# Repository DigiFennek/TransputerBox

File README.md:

# TransputerBox
This is the DosBox based TransputerBox

The interface is based on a LPC dual-core MPU. The Cortex-M4 is doing USB stuff while the Cortex-M0+ is talking to the IMSC012 Transpuer Link Interface. The MCU is also checking the health status of the power supply and the cooling system.

The host-side is based on a modified version of DOSBox. It emulates the IMSB008 or IMSB004 hardware and connets to the TransputerBox via USB.

Software:
  - DOSBox with USB-Bridge, Windows 10, Visual Studio 2019: [Link](https://github.com/DigiFennek/TransputerBox/tree/master/Visual%20Studio)
  - USB-Interface, based on NXP's LPC54114, MCUXPresso IDE v11: [Link](https://github.com/DigiFennek/TransputerBox/tree/master/MCUXpresso)
  - CPLD for the fancy Link-Leds, Lattice M4A5-64/32-10VC, ispLever Classic: [Link](https://github.com/DigiFennek/TransputerBox/tree/master/ispLEVER%20Classic/linkled)
  
Hardware:
  - Module for 4 TRAM's, Eagle Layout Editor: [Link](https://github.com/DigiFennek/TransputerBox/tree/master/Eagle/TB-4)
  - Backpanel with 7 slots, Eagle Layout Editor: [Link](https://github.com/DigiFennek/TransputerBox/tree/master/Eagle/BB-7)
  - USB Interface with Power Management, Current Sensor and HP-Display, Eagle Layout Editor: [Link](https://github.com/DigiFennek/TransputerBox/tree/master/Eagle/UB-1)
  - SIZE-1 TRAM with 128kB SRAM, Eagle Layout Editor: [Link](https://github.com/DigiFennek/TransputerBox/tree/master/Eagle/TM-2)    
  
Misc
  - Front Panels, www.schaeffer-ag.de "FRONTPLATTEN DESIGNER": [Link](https://github.com/DigiFennek/TransputerBox/tree/master/Schaeffer%20AG)

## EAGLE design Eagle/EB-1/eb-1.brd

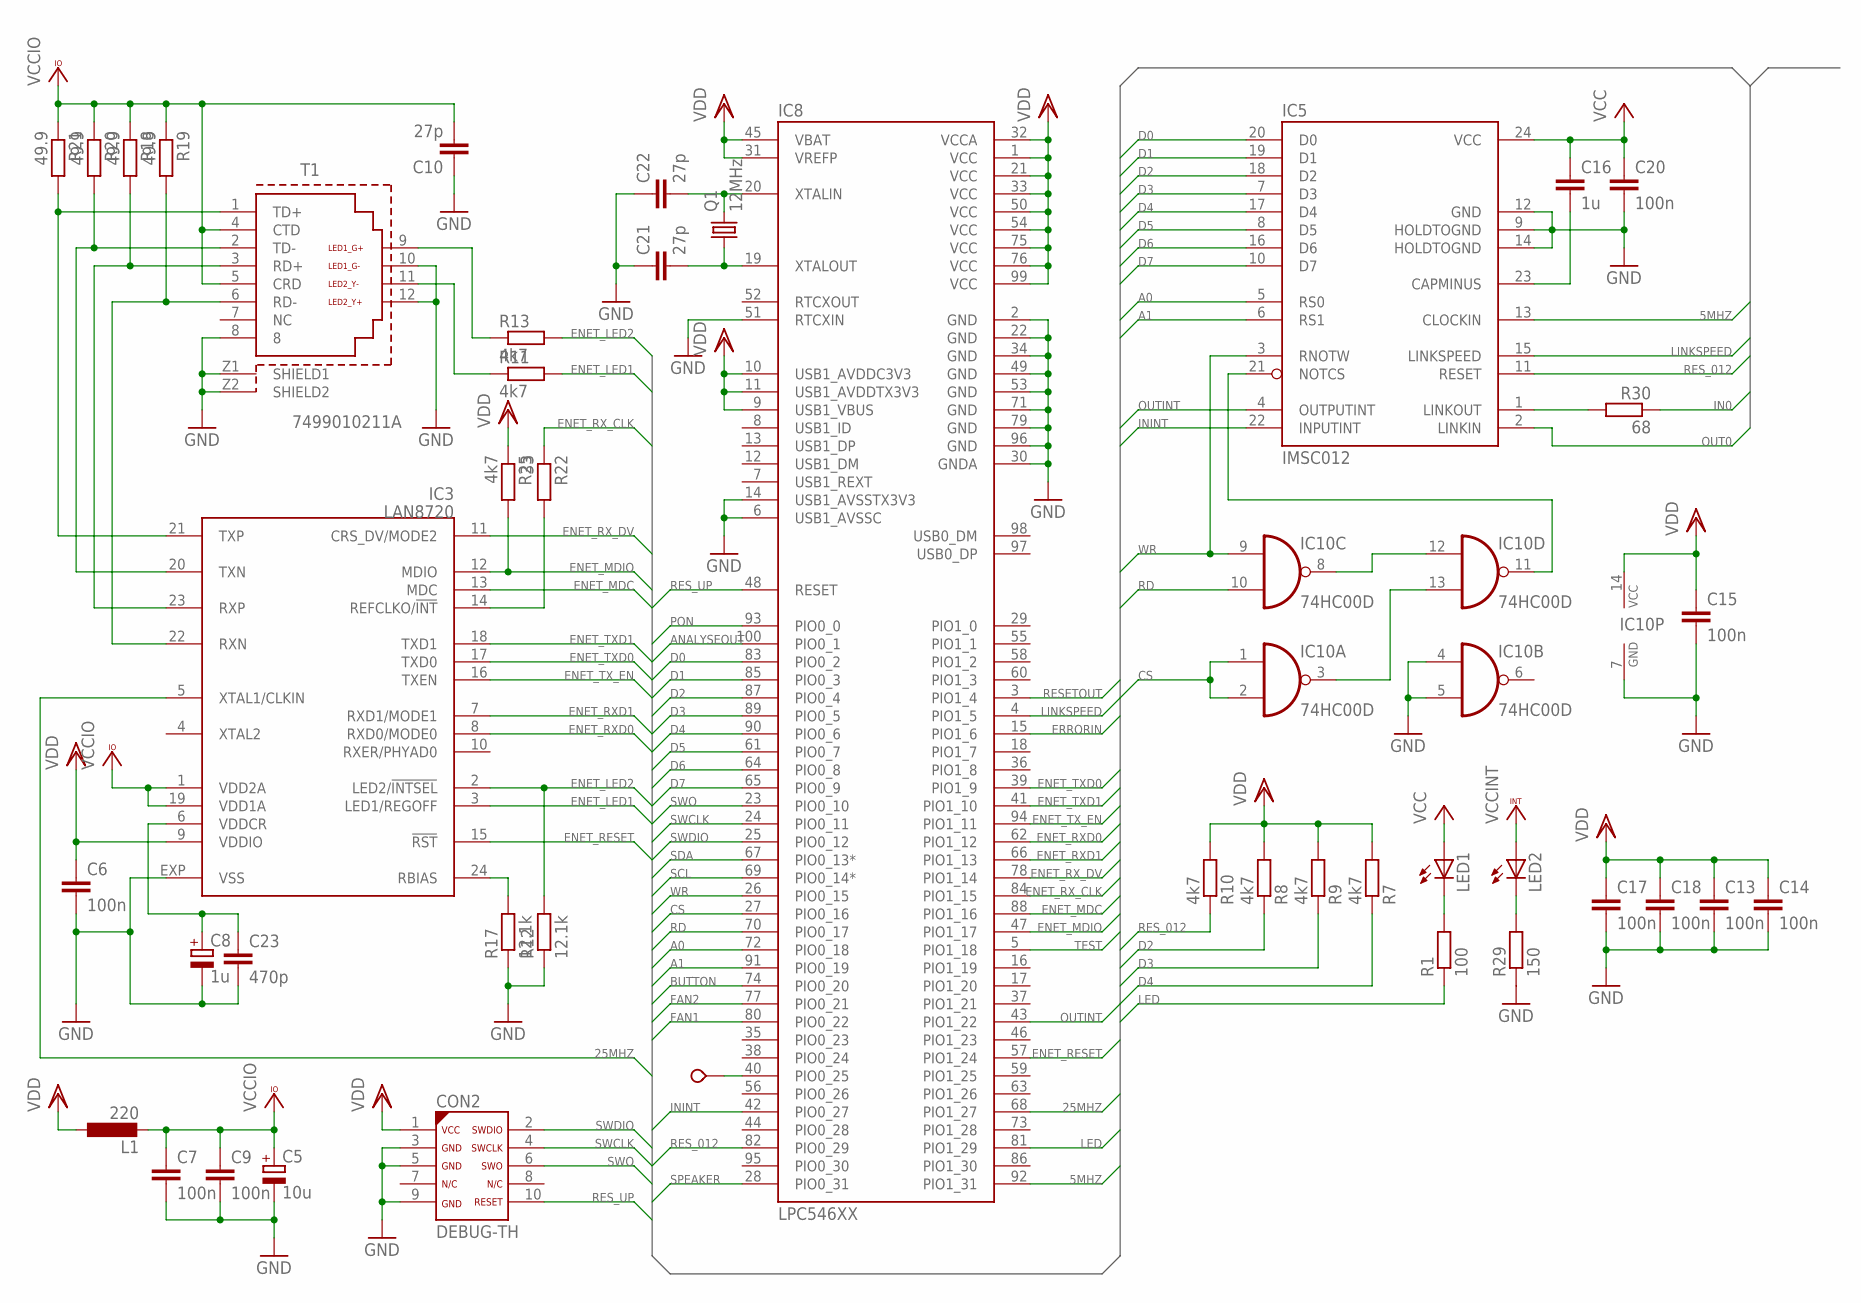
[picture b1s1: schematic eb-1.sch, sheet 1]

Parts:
C5: 10u; CT3216
C6, C7, C9, C13, C14, C15, C17, C18, C20: 100n; C1206; DIGIKEY 478-10855-1-ND
C8: 1u; CT3216
C10, C21, C22: 27p; C1206; DIGIKEY 478-10855-1-ND
C16: 1u; C1206; DIGIKEY 478-1567-1-ND
C23: 470p; C1206; DIGIKEY 478-10855-1-ND
CON2: DEBUG-TH; DIGIKEY 1175-1627-ND
IC3: LAN8720; QFN24
IC5: IMSC012; DIL24-3
IC8: LPC546XX; LQFP100
IC10: 74HC00D; SO14
L1: 220; L3216C
LED1, LED2: LEDSMT1206; 1206; DIGIKEY 160-1404-1-ND
Q1: 12MHz; HC49UP
R1: 100; R1206; DIGIKEY CR1206-FX-1000ELFCT-ND
R7, R8, R9, R10, R11, R13, R25: 4k7; R1206; DIGIKEY CR1206-FX-4701ELFCT-ND
R12, R17: 12.1k; R1206; DIGIKEY CR1206-FX-4701ELFCT-ND
R18, R19, R20, R21: 49.9; R1206; DIGIKEY CR1206-FX-4701ELFCT-ND
R22: 33; R1206; DIGIKEY CR1206-FX-4701ELFCT-ND
R29: 150; R1206; DIGIKEY CR1206-FX-1500ELFCT-ND
R30: 68; R1206; DIGIKEY CR1206-FX-68R0ELFCT-ND
T1: 7499010211A
TP2: TESTPOINT; VERO_TP

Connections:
5MHZ: IC5.13 (CLOCKIN), IC8.92 (PIO1_31)
25MHZ: IC3.5 (XTAL1/CLKIN), IC8.68 (PIO1_27)
A0: IC5.5 (RS0), IC8.72 (PIO0_18)
A1: IC5.6 (RS1), IC8.91 (PIO0_19)
ANALYSEOUT: IC8.100 (PIO0_1); also elsewhere on the board
BUTTON: IC8.74 (PIO0_20); also elsewhere on the board
CS: IC8.27 (PIO0_16), IC10.1 (I0), IC10.2 (I1)
D0: IC5.20 (D0), IC8.83 (PIO0_2)
D1: IC5.19 (D1), IC8.85 (PIO0_3)
D2: IC5.18 (D2), IC8.87 (PIO0_4), R8.1
D3: IC5.7 (D3), IC8.89 (PIO0_5), R9.1
D4: IC5.17 (D4), IC8.90 (PIO0_6), R7.1
D5: IC5.8 (D5), IC8.61 (PIO0_7)
D6: IC5.16 (D6), IC8.64 (PIO0_8)
D7: IC5.10 (D7), IC8.65 (PIO0_9)
ENET_LED1: IC3.3 (LED1/REGOFF), R11.2
ENET_LED2: IC3.2 (LED2/!INTSEL), R12.2, R13.2
ENET_MDC: IC3.13 (MDC), IC8.88 (PIO1_16)
ENET_MDIO: IC3.12 (MDIO), IC8.47 (PIO1_17), R25.2
ENET_RESET: IC3.15 (!RST), IC8.57 (PIO1_24)
ENET_RXD0: IC3.8 (RXD0/MODE0), IC8.62 (PIO1_12)
ENET_RXD1: IC3.7 (RXD1/MODE1), IC8.66 (PIO1_13)
ENET_RX_CLK: IC8.84 (PIO1_15), R22.1
ENET_RX_DV: IC3.11 (CRS_DV/MODE2), IC8.78 (PIO1_14)
ENET_TXD0: IC3.17 (TXD0), IC8.39 (PIO1_9)
ENET_TXD1: IC3.18 (TXD1), IC8.41 (PIO1_10)
ENET_TX_EN: IC3.16 (TXEN), IC8.94 (PIO1_11)
ERRORIN: IC8.15 (PIO1_6); also elsewhere on the board
FAN1: IC8.80 (PIO0_22); also elsewhere on the board
FAN2: IC8.77 (PIO0_21); also elsewhere on the board
GND: C5.-, C6.2, C7.2, C8.-, C9.2, C10.1, C13.2, C14.2, C15.2, C17.2, C18.2, C20.2, C21.1, C22.1, C23.2, CON2.3, CON2.5, CON2.9, IC3.EXP (VSS), IC5.9 (HOLDTOGND), IC5.12 (GND), IC5.14 (HOLDTOGND), IC8.2 (GND), IC8.6 (USB1_AVSSC), IC8.14 (USB1_AVSSTX3V3), IC8.22 (GND), IC8.30 (GNDA), IC8.34 (GND), IC8.49 (GND), IC8.51 (RTCXIN), IC8.53 (GND), IC8.71 (GND), IC8.79 (GND), IC8.96 (GND), IC10.4 (I0), IC10.5 (I1), IC10.7 (GND), R12.1, R17.1, R29.1, T1.8, T1.10 (LED1_G-), T1.12 (LED2_Y+), T1.Z1 (SHIELD1), T1.Z2 (SHIELD2); also elsewhere on the board
IN0: R30.1; also elsewhere on the board
ININT: IC5.22 (INPUTINT), IC8.42 (PIO0_27)
LED: IC8.81 (PIO1_29), R1.1
LINKSPEED: IC5.15 (LINKSPEED), IC8.4 (PIO1_5); also elsewhere on the board
unnamed: IC3.14 (REFCLKO/!INT), R22.2
unnamed: R13.1, T1.9 (LED1_G+)
unnamed: IC3.24 (RBIAS), R17.2
unnamed: R11.1, T1.11 (LED2_Y-)
unnamed: IC8.40 (PIO0_25), TP2.P$1
unnamed: C8.+, C23.1, IC3.6 (VDDCR)
unnamed: C22.2, IC8.20 (XTALIN), Q1.2
unnamed: C21.2, IC8.19 (XTALOUT), Q1.1
unnamed: IC5.1 (LINKOUT), R30.2
unnamed: IC5.21 (NOTCS), IC10.11 (O)
unnamed: C16.2, IC5.23 (CAPMINUS)
unnamed: LED2.C, R29.2
unnamed: LED1.C, R1.2
unnamed: IC10.8 (O), IC10.12 (I0)
unnamed: IC10.3 (O), IC10.13 (I1)
OUT0: IC5.2 (LINKIN); also elsewhere on the board
OUTINT: IC5.4 (OUTPUTINT), IC8.43 (PIO1_22)
PON: IC8.93 (PIO0_0); also elsewhere on the board
RD: IC8.70 (PIO0_17), IC10.10 (I1)
RESETOUT: IC8.3 (PIO1_4); also elsewhere on the board
RES_012: IC5.11 (RESET), IC8.82 (PIO0_29), R10.1
RES_UP: CON2.10, IC8.48 (RESET)
RX_N: IC3.22 (RXN), R19.2, T1.6 (RD-)
RX_P: IC3.23 (RXP), R18.2, T1.3 (RD+)
SCL: IC8.69 (PIO0_14*); also elsewhere on the board
SDA: IC8.67 (PIO0_13*); also elsewhere on the board
SPEAKER: IC8.28 (PIO0_31); also elsewhere on the board
SWCLK: CON2.4, IC8.24 (PIO0_11)
SWDIO: CON2.2, IC8.25 (PIO0_12)
SWO: CON2.6, IC8.23 (PIO0_10)
TEST: IC8.5 (PIO1_18); also elsewhere on the board
TX_N: IC3.20 (TXN), R20.2, T1.2 (TD-)
TX_P: IC3.21 (TXP), R21.2, T1.1 (TD+)
VCC: C16.1, C20.1, IC5.24 (VCC), LED1.A; also elsewhere on the board
VCCINT: LED2.A; also elsewhere on the board
VCCIO: C5.+, C7.1, C9.1, C10.2, IC3.1 (VDD2A), IC3.19 (VDD1A), L1.2, R18.1, R19.1, R20.1, R21.1, T1.4 (CTD), T1.5 (CRD)
VDD: C6.1, C13.1, C14.1, C15.1, C17.1, C18.1, CON2.1, IC3.9 (VDDIO), IC8.1 (VCC), IC8.9 (USB1_VBUS), IC8.10 (USB1_AVDDC3V3), IC8.11 (USB1_AVDDTX3V3), IC8.21 (VCC), IC8.31 (VREFP), IC8.32 (VCCA), IC8.33 (VCC), IC8.45 (VBAT), IC8.50 (VCC), IC8.54 (VCC), IC8.75 (VCC), IC8.76 (VCC), IC8.99 (VCC), IC10.14 (VCC), L1.1, R7.2, R8.2, R9.2, R10.2, R25.1; also elsewhere on the board
WR: IC5.3 (RNOTW), IC8.26 (PIO0_15), IC10.9 (I0)

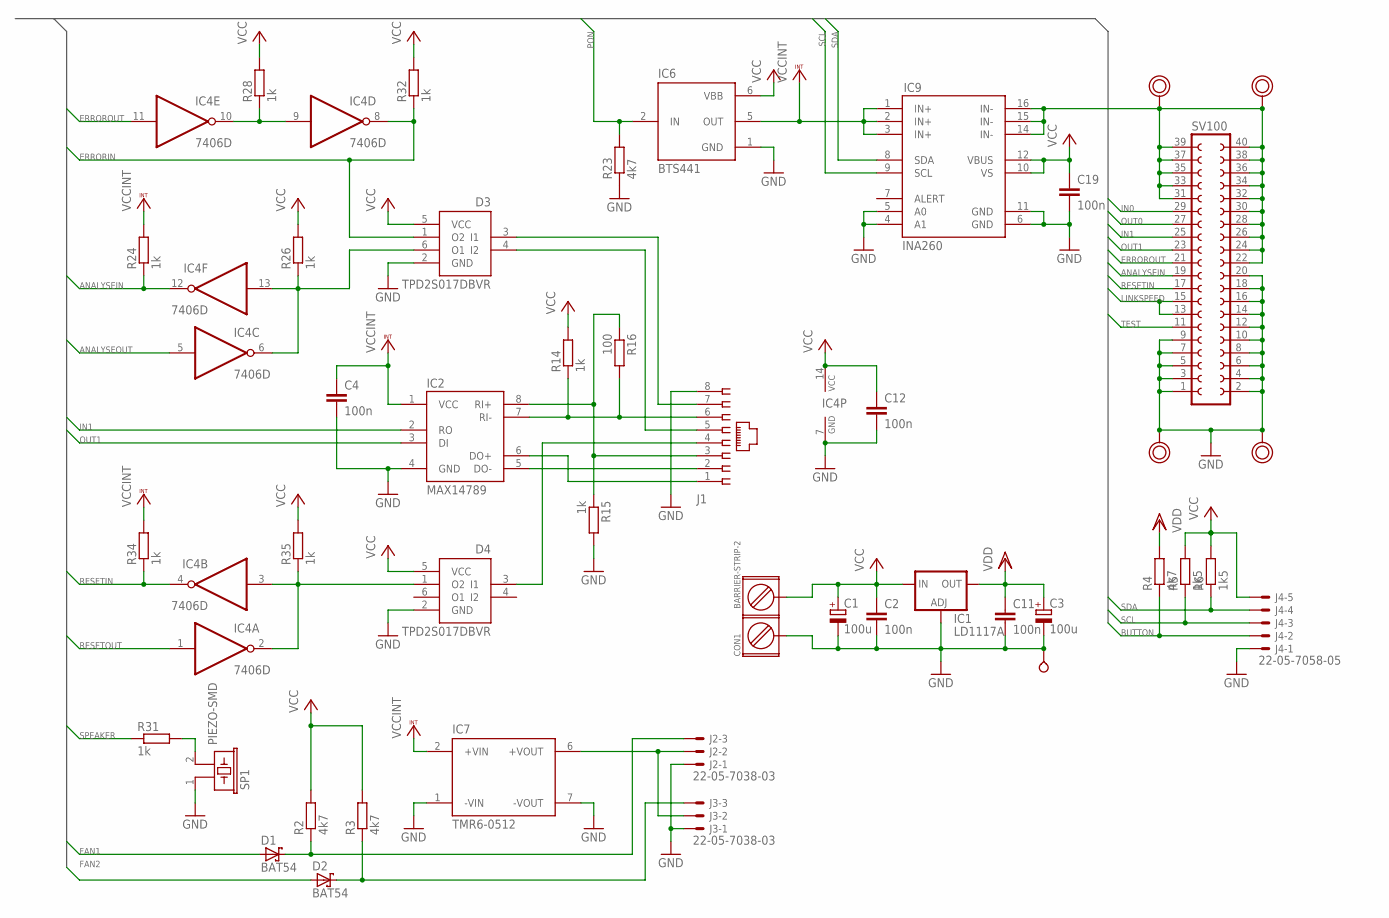
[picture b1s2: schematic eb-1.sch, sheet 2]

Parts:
C1, C3: 100u; SMC_B; DIGIKEY 478-5801-1-ND
C2, C4, C11, C12, C19: 100n; C1206; DIGIKEY 478-10855-1-ND
CON1: BARRIER-STRIP-2; DIGIKEY WM13929-ND
D1, D2: BAT54; SOT23; DIGIKEY BAT54FSCT-ND
D3, D4: TPD2S017DBVR; SOT23-6
IC1: LD1117A; SOT223; DIGIKEY 497-1228-1-ND
IC2: MAX14789; SO8; DIGIKEY MAX14789EGSA+-ND
IC4: 7406D; SO14
IC6: BTS441; TO263-4; DIGIKEY BTS441TGATMA1CT-ND
IC7: TMR6-0512; DIGIKEY 1951-2391-ND
IC9: INA260; TSSOP-16; DIGIKEY 296-47777-1-ND
J1: 555164-1; DIGIKEY A31442-ND
J2, J3: 22-05-7038-03; 7395-03; DIGIKEY WM2785-ND
J4: 22-05-7058-05; 7395-05; DIGIKEY WM2787-ND
R2, R3, R4, R23: 4k7; R1206; DIGIKEY CR1206-FX-4701ELFCT-ND
R5, R6: 1k5; R1206; DIGIKEY CR1206-FX-1501ELFCT-ND
R14, R15, R24, R26, R28, R31, R32, R34, R35: 1k; R1206; DIGIKEY CR1206-FX-1001ELFCT-ND
R16: 100; R1206; DIGIKEY CR1206-FX-1000ELFCT-ND
SCREW1, SCREW2, SCREW3, SCREW4: POWERPAD
SP1: PIEZO-SMD; DIGIKEY 490-9647-1-ND
SV100: FE20-2
TP1: TESTPOINT; VERO_TP

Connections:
ANALYSEIN: IC4.12 (O), R24.1, SV100.19
ANALYSEOUT: IC4.5 (I); also elsewhere on the board
BUTTON: J4.2, R4.1; also elsewhere on the board
ERRORIN: D3.1 (O2), IC4.8 (O), R32.1; also elsewhere on the board
ERROROUT: IC4.11 (I), SV100.21
FAN1: D1.1 (A); also elsewhere on the board
FAN2: D2.1 (A); also elsewhere on the board
GND: C1.-, C2.2, C3.-, C4.2, C11.2, C12.2, C19.2, CON1.1, D3.2 (GND), D4.2 (GND), IC1.1 (ADJ), IC2.4 (GND), IC4.7 (GND), IC6.1 (GND), IC7.1 (-VIN), IC7.7 (-VOUT), IC9.4 (A1), IC9.5 (A0), IC9.6 (GND), IC9.11 (GND), J1.8, J2.1, J3.1, J4.1, R15.2, R23.1, SCREW2.P$1, SCREW4.P$1, SP1.1, SV100.1, SV100.2, SV100.3, SV100.4, SV100.5, SV100.6, SV100.7, SV100.8, SV100.9, SV100.10, SV100.12, SV100.14, SV100.16, SV100.18, SV100.20, TP1.P$1; also elsewhere on the board
IN0: SV100.29; also elsewhere on the board
IN1: IC2.2 (RO), SV100.25
LINKSPEED: SV100.13, SV100.15; also elsewhere on the board
unnamed: D4.1 (O2), IC4.2 (O), IC4.3 (I), R35.1
unnamed: IC4.9 (I), IC4.10 (O), R28.1
unnamed: IC2.6 (DO+), J1.1
unnamed: IC2.5 (DO-), J1.2
unnamed: D3.3 (I1), J1.7
unnamed: D4.3 (I1), J1.4
unnamed: D3.4 (I2), J1.5
unnamed: D3.6 (O1), IC4.6 (O), IC4.13 (I), R26.1
unnamed: IC2.8 (RI+), J1.3, R15.1, R16.1
unnamed: IC2.7 (RI-), J1.6, R14.1, R16.2
unnamed: D2.3 (C), J3.3, R3.1
unnamed: IC9.14 (IN-), IC9.15 (IN-), IC9.16 (IN-), SCREW1.P$1, SCREW3.P$1, SV100.22, SV100.24, SV100.26, SV100.28, SV100.30, SV100.31, SV100.32, SV100.33, SV100.34, SV100.35, SV100.36, SV100.37, SV100.38, SV100.39, SV100.40
unnamed: D1.3 (C), J2.3, R2.1
unnamed: R31.2, SP1.2
unnamed: IC7.6 (+VOUT), J2.2, J3.2
OUT0: SV100.27; also elsewhere on the board
OUT1: IC2.3 (DI), SV100.23
PON: IC6.2 (IN), R23.2; also elsewhere on the board
RESETIN: IC4.4 (O), R34.1, SV100.17
RESETOUT: IC4.1 (I); also elsewhere on the board
SCL: IC9.9 (SCL), J4.4, R6.1; also elsewhere on the board
SDA: IC9.8 (SDA), J4.3, R5.1; also elsewhere on the board
SPEAKER: R31.1; also elsewhere on the board
TEST: SV100.11; also elsewhere on the board
VCC: C1.+, C2.1, C12.1, C19.1, CON1.2, D3.5 (VCC), D4.5 (VCC), IC1.3 (IN), IC4.14 (VCC), IC6.6 (VBB), IC9.10 (VS), IC9.12 (VBUS), J4.5, R2.2, R3.2, R5.2, R6.2, R14.2, R26.2, R28.2, R32.2, R35.2; also elsewhere on the board
VCCINT: C4.1, IC2.1 (VCC), IC6.5 (OUT), IC7.2 (+VIN), IC9.1 (IN+), IC9.2 (IN+), IC9.3 (IN+), R24.2, R34.2; also elsewhere on the board
VDD: C3.+, C11.1, IC1.2 (OUT), R4.2; also elsewhere on the board

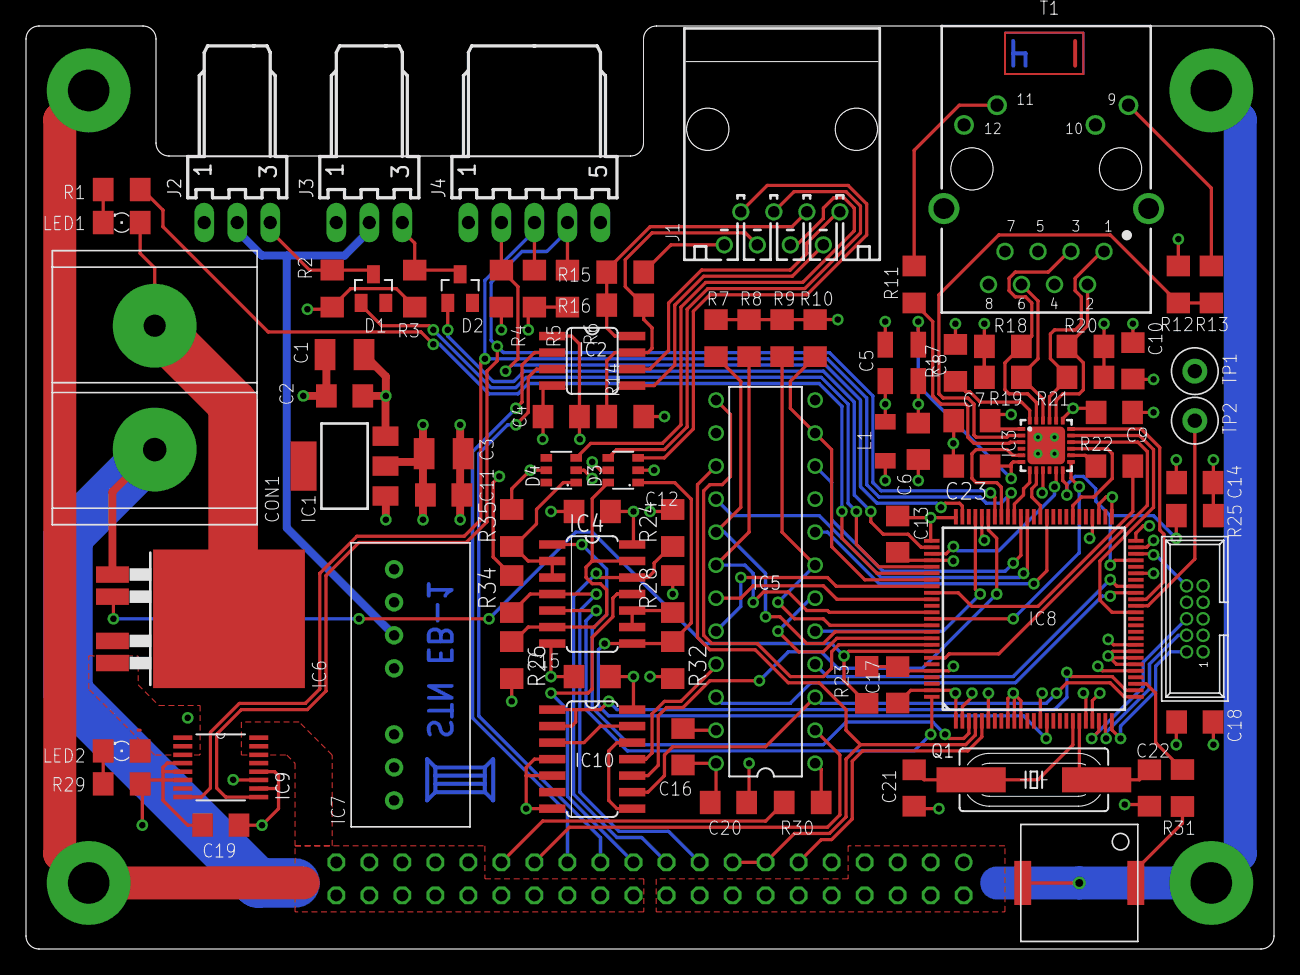
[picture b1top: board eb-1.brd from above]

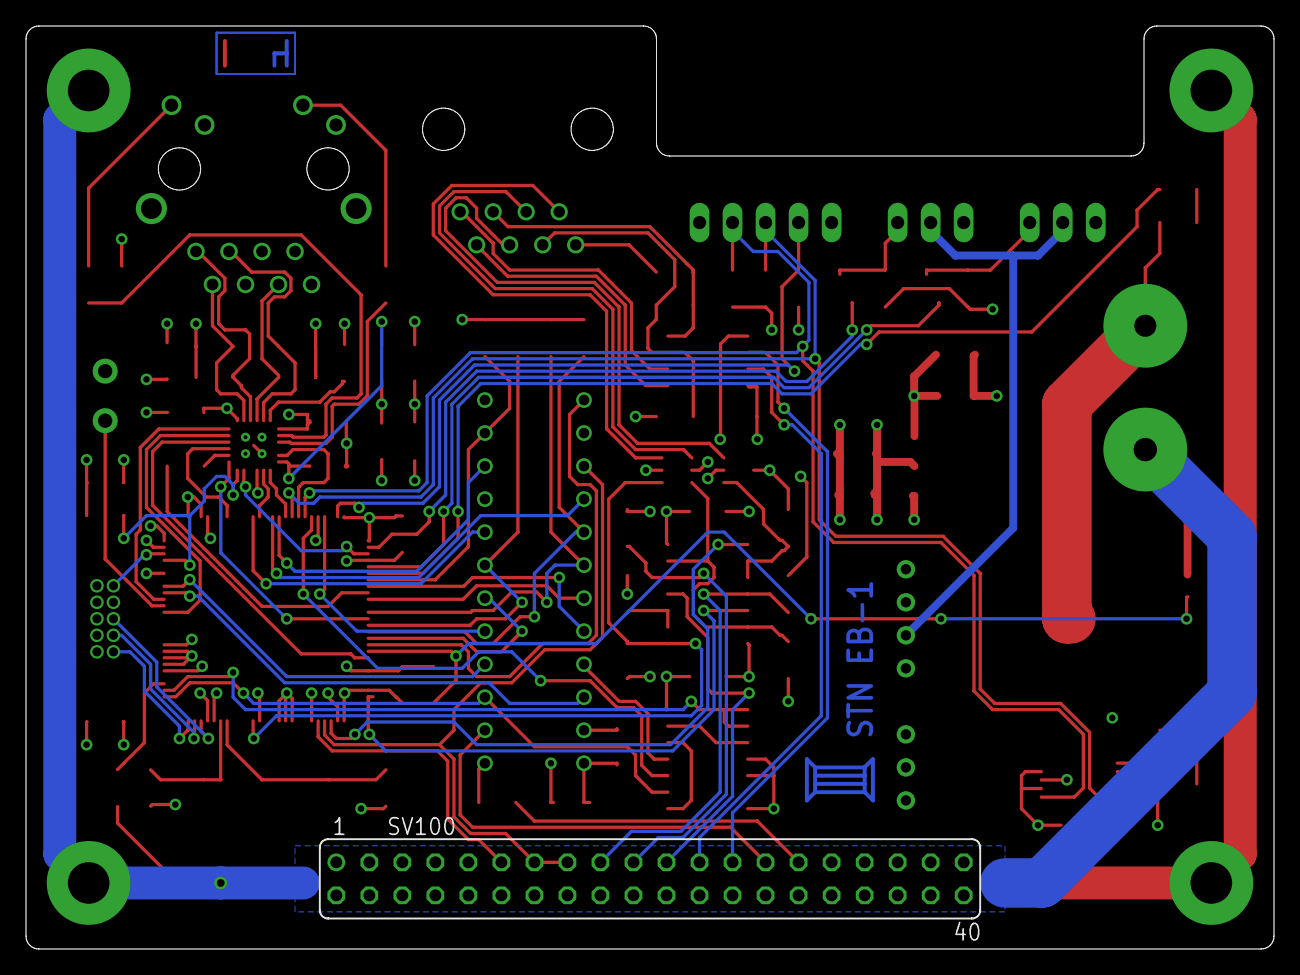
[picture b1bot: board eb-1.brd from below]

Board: 6 copper layers, 96.0 x 71.0 mm, 91 parts (2 on the bottom side), 93 nets.

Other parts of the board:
U$1: LAYER14
U$100: LOGO

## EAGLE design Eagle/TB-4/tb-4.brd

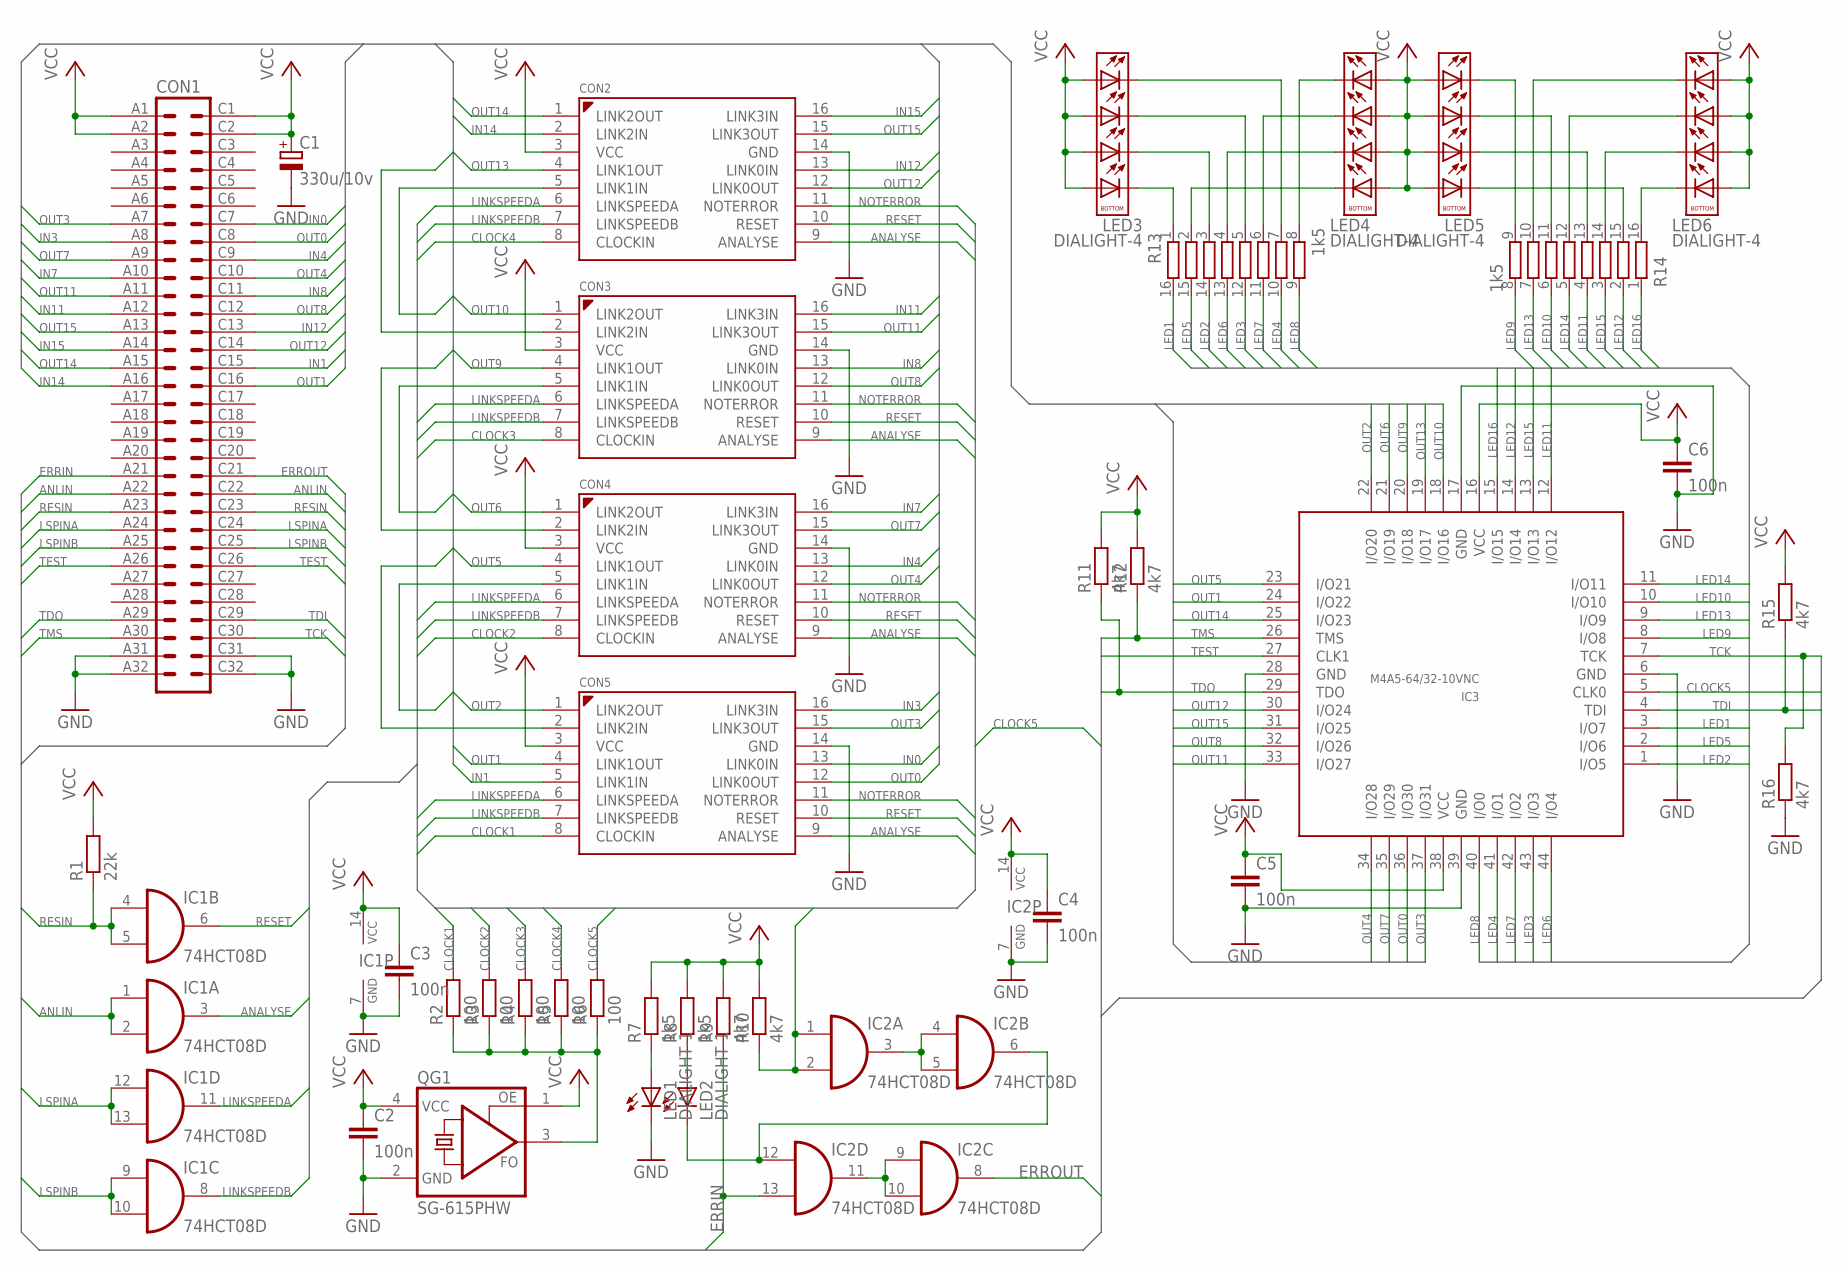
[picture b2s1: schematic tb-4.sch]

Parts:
C1: 330u/10v; SMC_E
C2, C3, C4, C5, C6: 100n; C1206
CON1: HARTING 09 03 164 6921; EUROPAKARTE-TB4
CON2, CON3, CON4, CON5: TRAM-1; TRAM-1-MB
IC1, IC2: 74HCT08D; SO14
IC3: M4A5-64/32-10VNC; TQFP-44
LED1, LED2: DIALIGHT-1
LED3, LED4, LED5, LED6: DIALIGHT-4
QG1: SG-615PHW; SG-615
R1: 22k; R1206
R2, R3, R4, R5, R6: 100; R1206
R7, R8: 1k5; R1206
R9, R10, R11, R12, R15, R16: 4k7; R1206
R13, R14: 1k5; 4816P

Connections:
ANALYSE: CON2.9 (ANALYSE), CON3.9 (ANALYSE), CON4.9 (ANALYSE), CON5.9 (ANALYSE), IC1.3 (O)
ANLIN: CON1.A22, CON1.C22, IC1.1 (I0), IC1.2 (I1)
CLOCK1: CON5.8 (CLOCKIN), R2.2
CLOCK2: CON4.8 (CLOCKIN), R3.2
CLOCK3: CON3.8 (CLOCKIN), R4.2
CLOCK4: CON2.8 (CLOCKIN), R5.2
CLOCK5: IC3.5 (CLK0), R6.2
ERRIN: CON1.A21, IC2.13 (I1), R9.1
ERROUT: CON1.C21, IC2.8 (O)
GND: C1.-, C2.2, C3.2, C4.2, C5.2, C6.2, CON1.A31, CON1.A32, CON1.C31, CON1.C32, CON2.14 (GND), CON3.14 (GND), CON4.14 (GND), CON5.14 (GND), IC1.7 (GND), IC2.7 (GND), IC3.6 (GND), IC3.17 (GND), IC3.28 (GND), IC3.39 (GND), LED1.C1 (C), QG1.2 (GND), R16.1
IN0: CON1.C7, CON5.13 (LINK0IN)
IN1: CON1.C15, CON5.5 (LINK1IN)
IN3: CON1.A8, CON5.16 (LINK3IN)
IN4: CON1.C9, CON4.13 (LINK0IN)
IN7: CON1.A10, CON4.16 (LINK3IN)
IN8: CON1.C11, CON3.13 (LINK0IN)
IN11: CON1.A12, CON3.16 (LINK3IN)
IN12: CON1.C13, CON2.13 (LINK0IN)
IN14: CON1.A16, CON2.2 (LINK2IN)
IN15: CON1.A14, CON2.16 (LINK3IN)
LED1: IC3.3 (I/O7), R13.16
LED2: IC3.1 (I/O5), R13.14
LED3: IC3.43 (I/O3), R13.12
LED4: IC3.41 (I/O1), R13.10
LED5: IC3.2 (I/O6), R13.15
LED6: IC3.44 (I/O4), R13.13
LED7: IC3.42 (I/O2), R13.11
LED8: IC3.40 (I/O0), R13.9
LED9: IC3.8 (I/O8), R14.8
LED10: IC3.10 (I/O10), R14.6
LED11: IC3.12 (I/O12), R14.4
LED12: IC3.14 (I/O14), R14.2
LED13: IC3.9 (I/O9), R14.7
LED14: IC3.11 (I/O11), R14.5
LED15: IC3.13 (I/O13), R14.3
LED16: IC3.15 (I/O15), R14.1
LINKSPEEDA: CON2.6 (LINKSPEEDA), CON3.6 (LINKSPEEDA), CON4.6 (LINKSPEEDA), CON5.6 (LINKSPEEDA), IC1.11 (O)
LINKSPEEDB: CON2.7 (LINKSPEEDB), CON3.7 (LINKSPEEDB), CON4.7 (LINKSPEEDB), CON5.7 (LINKSPEEDB), IC1.8 (O)
LSPINA: CON1.A24, CON1.C24, IC1.12 (I0), IC1.13 (I1)
LSPINB: CON1.A25, CON1.C25, IC1.9 (I0), IC1.10 (I1)
unnamed: QG1.3 (FO), R2.1, R3.1, R4.1, R5.1, R6.1
unnamed: LED2.A1 (A), R8.1
unnamed: IC2.3 (O), IC2.4 (I0), IC2.5 (I1)
unnamed: LED1.A1 (A), R7.1
unnamed: LED3.C1, R13.1
unnamed: LED4.C1, R13.2
unnamed: LED3.C2, R13.3
unnamed: LED4.C2, R13.4
unnamed: LED4.C3, R13.6
unnamed: LED4.C4, R13.8
unnamed: LED3.C4, R13.7
unnamed: LED3.C3, R13.5
unnamed: LED5.C1, R14.15
unnamed: LED6.C1, R14.16
unnamed: LED6.C2, R14.14
unnamed: LED5.C2, R14.13
unnamed: LED6.C3, R14.12
unnamed: LED5.C3, R14.11
unnamed: LED6.C4, R14.10
unnamed: LED5.C4, R14.9
unnamed: IC2.9 (I0), IC2.10 (I1), IC2.11 (O)
unnamed: IC2.6 (O), IC2.12 (I0), LED2.C1 (C)
NOTERROR: CON2.11 (NOTERROR), CON3.11 (NOTERROR), CON4.11 (NOTERROR), CON5.11 (NOTERROR), IC2.1 (I0), IC2.2 (I1), R10.1
OUT0: CON1.C8, CON5.12 (LINK0OUT), IC3.36 (I/O30)
OUT1: CON1.C16, CON5.4 (LINK1OUT), IC3.24 (I/O22)
OUT2: CON4.5 (LINK1IN), CON5.1 (LINK2OUT), IC3.22 (I/O20)
OUT3: CON1.A7, CON5.15 (LINK3OUT), IC3.37 (I/O31)
OUT4: CON1.C10, CON4.12 (LINK0OUT), IC3.34 (I/O28)
OUT5: CON4.4 (LINK1OUT), CON5.2 (LINK2IN), IC3.23 (I/O21)
OUT6: CON3.5 (LINK1IN), CON4.1 (LINK2OUT), IC3.21 (I/O19)
OUT7: CON1.A9, CON4.15 (LINK3OUT), IC3.35 (I/O29)
OUT8: CON1.C12, CON3.12 (LINK0OUT), IC3.32 (I/O26)
OUT9: CON3.4 (LINK1OUT), CON4.2 (LINK2IN), IC3.20 (I/O18)
OUT10: CON2.5 (LINK1IN), CON3.1 (LINK2OUT), IC3.18 (I/O16)
OUT11: CON1.A11, CON3.15 (LINK3OUT), IC3.33 (I/O27)
OUT12: CON1.C14, CON2.12 (LINK0OUT), IC3.30 (I/O24)
OUT13: CON2.4 (LINK1OUT), CON3.2 (LINK2IN), IC3.19 (I/O17)
OUT14: CON1.A15, CON2.1 (LINK2OUT), IC3.25 (I/O23)
OUT15: CON1.A13, CON2.15 (LINK3OUT), IC3.31 (I/O25)
RESET: CON2.10 (RESET), CON3.10 (RESET), CON4.10 (RESET), CON5.10 (RESET), IC1.6 (O)
RESIN: CON1.A23, CON1.C23, IC1.4 (I0), IC1.5 (I1), R1.1
TCK: CON1.C30, IC3.7 (TCK), R16.2
TDI: CON1.C29, IC3.4 (TDI), R15.1
TDO: CON1.A29, IC3.29 (TDO), R11.1
TEST: CON1.A26, CON1.C26, IC3.27 (CLK1)
TMS: CON1.A30, IC3.26 (TMS), R12.1
VCC: C1.+, C2.1, C3.1, C4.1, C5.1, C6.1, CON1.A1, CON1.A2, CON1.C1, CON1.C2, CON2.3 (VCC), CON3.3 (VCC), CON4.3 (VCC), CON5.3 (VCC), IC1.14 (VCC), IC2.14 (VCC), IC3.16 (VCC), IC3.38 (VCC), LED3.A1, LED3.A2, LED3.A3, LED3.A4, LED4.A1, LED4.A2, LED4.A3, LED4.A4, LED5.A1, LED5.A2, LED5.A3, LED5.A4, LED6.A1, LED6.A2, LED6.A3, LED6.A4, QG1.1 (OE), QG1.4 (VCC), R1.2, R7.2, R8.2, R9.2, R10.2, R11.2, R12.2, R15.2

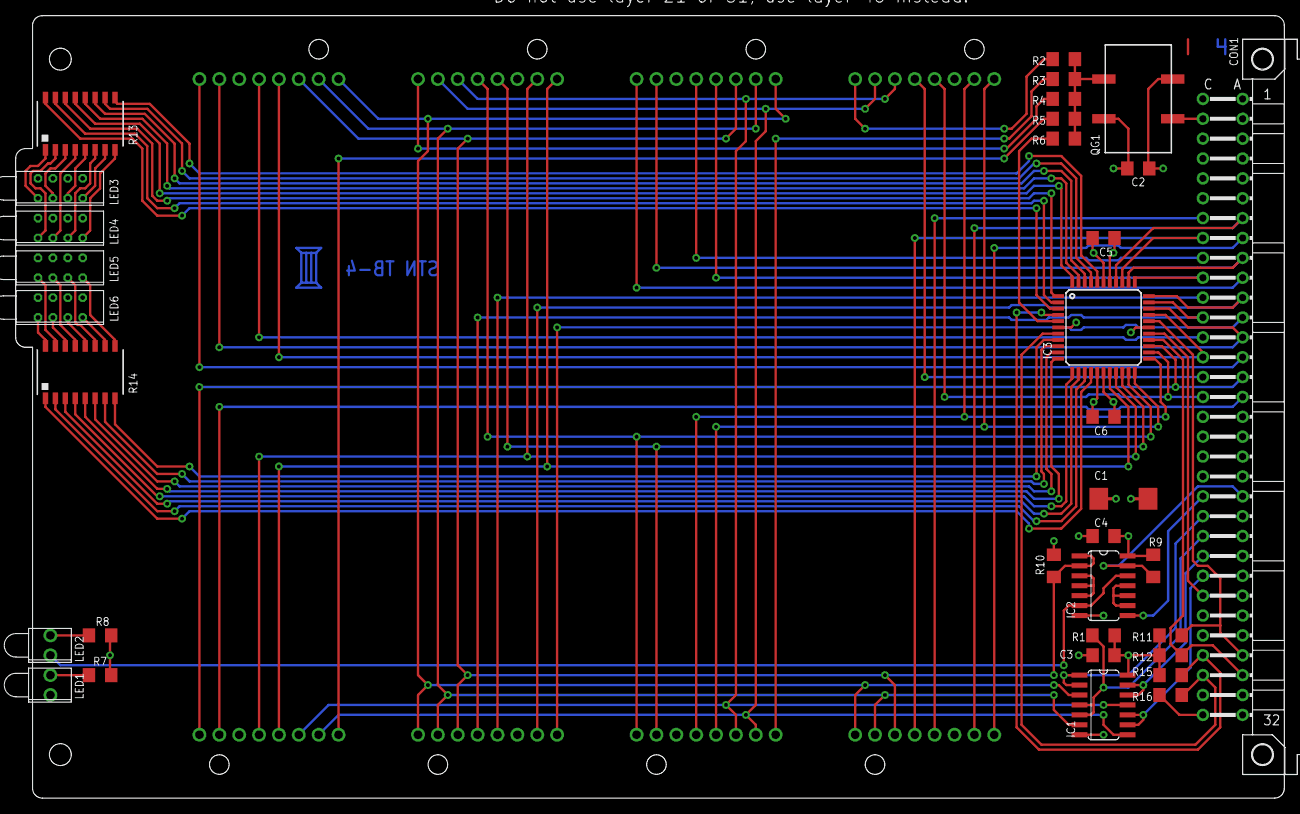
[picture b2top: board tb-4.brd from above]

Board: 4 copper layers, 162.2 x 100.0 mm, 39 parts (1 on the bottom side), 87 nets.

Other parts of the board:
U$2: LOGO
U$3: LAYER14

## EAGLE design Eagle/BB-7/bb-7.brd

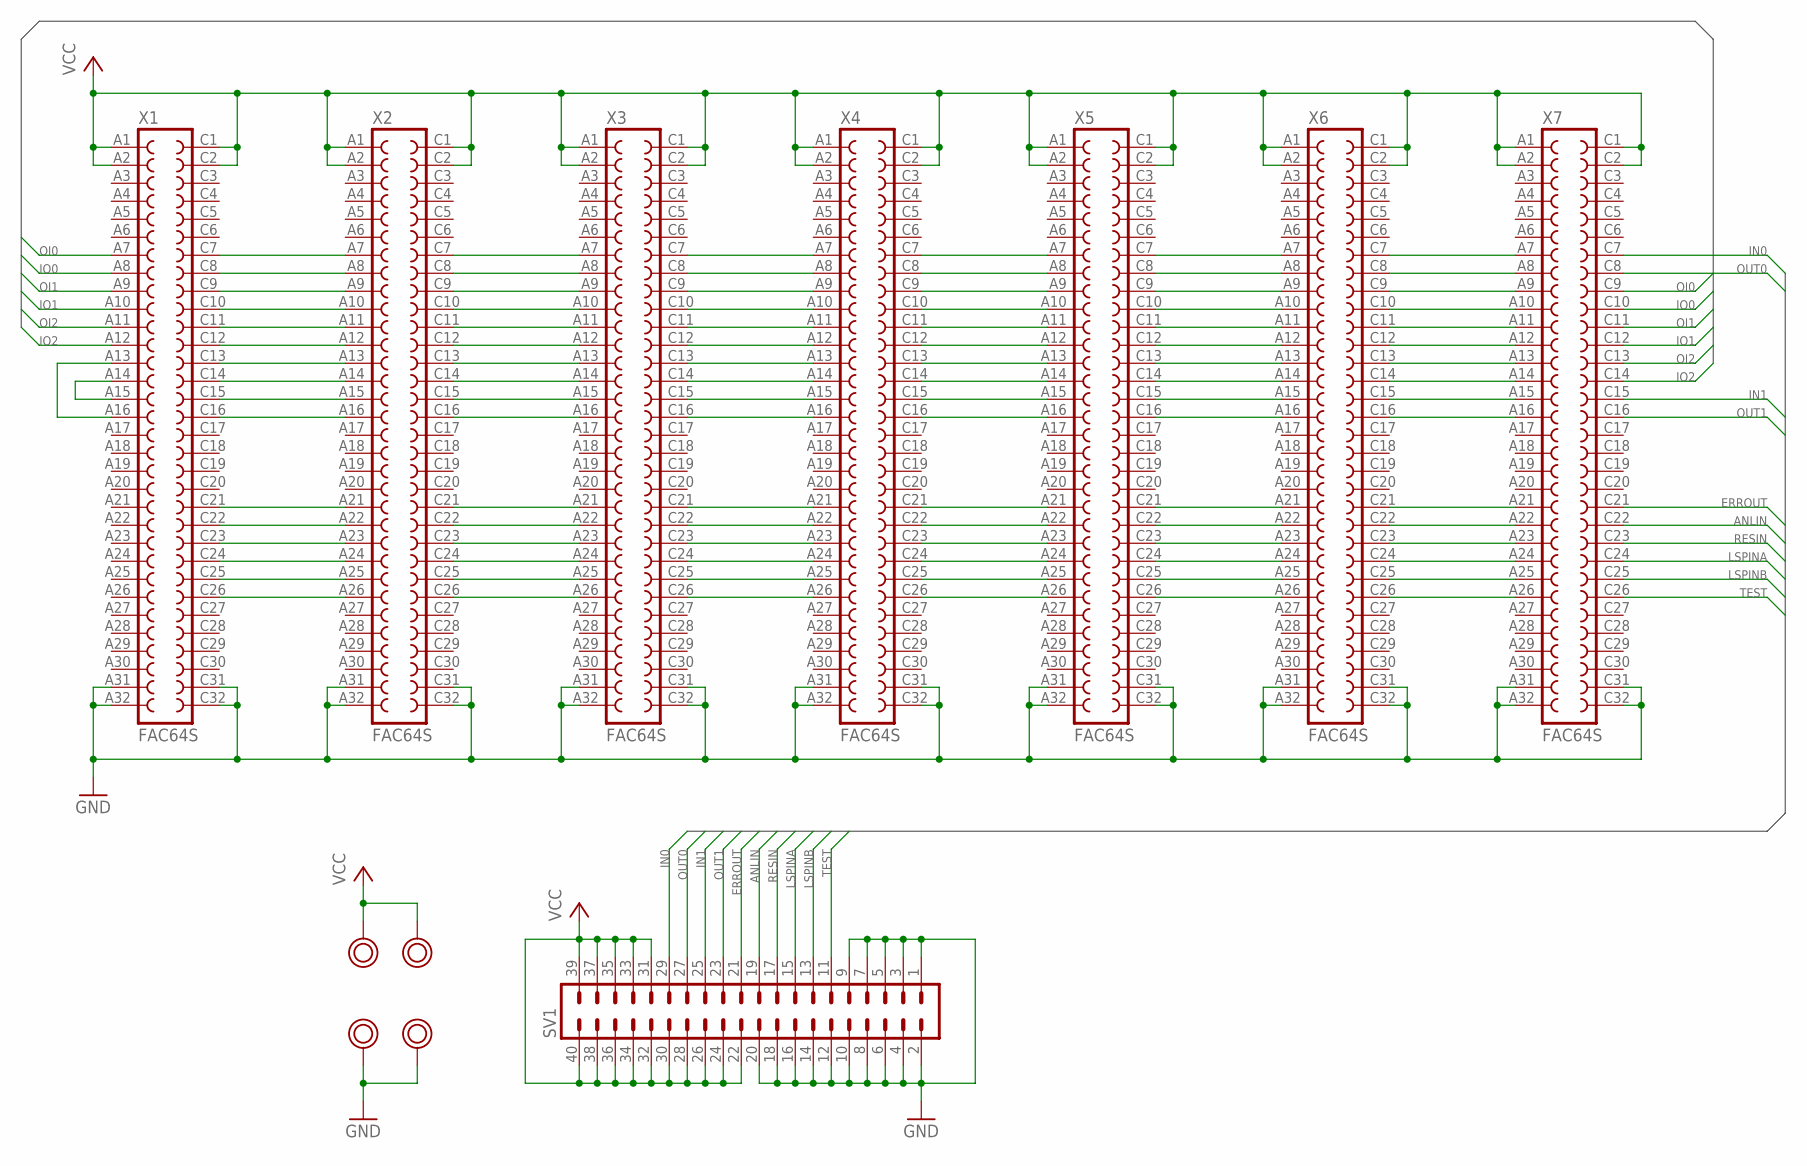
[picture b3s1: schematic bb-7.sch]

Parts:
SV1: MA20-2
U$3, U$4, U$5, U$6: POWERPAD
X1, X2, X3, X4, X5, X6, X7: FAC64S

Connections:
ANLIN: SV1.19, X7.C22
ERROUT: SV1.21, X7.C21
GND: SV1.1, SV1.2, SV1.3, SV1.4, SV1.5, SV1.6, SV1.7, SV1.8, SV1.9, SV1.10, SV1.12, SV1.14, SV1.16, SV1.18, SV1.20, U$3.P$1, U$4.P$1, X1.A31, X1.A32, X1.C31, X1.C32, X2.A31, X2.A32, X2.C31, X2.C32, X3.A31, X3.A32, X3.C31, X3.C32, X4.A31, X4.A32, X4.C31, X4.C32, X5.A31, X5.A32, X5.C31, X5.C32, X6.A31, X6.A32, X6.C31, X6.C32, X7.A31, X7.A32, X7.C31, X7.C32
IN0: SV1.29, X7.C7
IN1: SV1.25, X7.C15
IO0: X1.A8, X7.C10
IO1: X1.A10, X7.C12
IO2: X1.A12, X7.C14
LSPINA: SV1.15, X7.C24
LSPINB: SV1.13, X7.C25
unnamed: X1.A13, X1.A16
unnamed: X1.A14, X1.A15
unnamed: X4.C7, X5.A7
unnamed: X2.C7, X3.A7
unnamed: X2.C8, X3.A8
unnamed: X2.C9, X3.A9
unnamed: X1.C7, X2.A7
unnamed: X1.C8, X2.A8
unnamed: X1.C9, X2.A9
unnamed: X1.C10, X2.A10
unnamed: X1.C11, X2.A11
unnamed: X1.C12, X2.A12
unnamed: X1.C13, X2.A13
unnamed: X1.C14, X2.A14
unnamed: X1.C15, X2.A15
unnamed: X1.C16, X2.A16
unnamed: X2.C10, X3.A10
unnamed: X2.C11, X3.A11
unnamed: X2.C12, X3.A12
unnamed: X2.C13, X3.A13
unnamed: X1.C21, X2.A21
unnamed: X1.C22, X2.A22
unnamed: X1.C23, X2.A23
unnamed: X1.C24, X2.A24
unnamed: X1.C25, X2.A25
unnamed: X1.C26, X2.A26
unnamed: X2.C14, X3.A14
unnamed: X2.C15, X3.A15
unnamed: X2.C16, X3.A16
unnamed: X2.C21, X3.A21
unnamed: X2.C22, X3.A22
unnamed: X2.C23, X3.A23
unnamed: X2.C24, X3.A24
unnamed: X2.C25, X3.A25
unnamed: X2.C26, X3.A26
unnamed: X4.C8, X5.A8
unnamed: X4.C9, X5.A9
unnamed: X3.C7, X4.A7
unnamed: X3.C8, X4.A8
unnamed: X3.C9, X4.A9
unnamed: X3.C10, X4.A10
unnamed: X3.C11, X4.A11
unnamed: X3.C12, X4.A12
unnamed: X3.C13, X4.A13
unnamed: X3.C14, X4.A14
unnamed: X3.C15, X4.A15
unnamed: X3.C16, X4.A16
unnamed: X3.C21, X4.A21
unnamed: X3.C22, X4.A22
unnamed: X3.C23, X4.A23
unnamed: X3.C24, X4.A24
unnamed: X3.C25, X4.A25
unnamed: X3.C26, X4.A26
unnamed: X4.C10, X5.A10
unnamed: X4.C11, X5.A11
unnamed: X4.C12, X5.A12
unnamed: X4.C13, X5.A13
unnamed: X4.C14, X5.A14
unnamed: X4.C15, X5.A15
unnamed: X4.C16, X5.A16
unnamed: X4.C21, X5.A21
unnamed: X4.C22, X5.A22
unnamed: X4.C23, X5.A23
unnamed: X4.C24, X5.A24
unnamed: X4.C25, X5.A25
unnamed: X4.C26, X5.A26
unnamed: X5.C7, X6.A7
unnamed: X5.C8, X6.A8
unnamed: X5.C9, X6.A9
unnamed: X5.C10, X6.A10
unnamed: X5.C11, X6.A11
unnamed: X5.C12, X6.A12
unnamed: X5.C13, X6.A13
unnamed: X5.C14, X6.A14
unnamed: X5.C15, X6.A15
unnamed: X5.C16, X6.A16
unnamed: X5.C21, X6.A21
unnamed: X5.C22, X6.A22
unnamed: X5.C23, X6.A23
unnamed: X5.C24, X6.A24
unnamed: X5.C25, X6.A25
unnamed: X5.C26, X6.A26
unnamed: X6.C7, X7.A7
unnamed: X6.C8, X7.A8
unnamed: X6.C9, X7.A9
unnamed: X6.C10, X7.A10
unnamed: X6.C11, X7.A11
unnamed: X6.C12, X7.A12
unnamed: X6.C13, X7.A13
unnamed: X6.C14, X7.A14
unnamed: X6.C15, X7.A15
unnamed: X6.C16, X7.A16
unnamed: X6.C21, X7.A21
unnamed: X6.C22, X7.A22
unnamed: X6.C23, X7.A23
unnamed: X6.C24, X7.A24
unnamed: X6.C25, X7.A25
unnamed: X6.C26, X7.A26
OI0: X1.A7, X7.C9
OI1: X1.A9, X7.C11
OI2: X1.A11, X7.C13
OUT0: SV1.27, X7.C8
OUT1: SV1.23, X7.C16
RESIN: SV1.17, X7.C23
TEST: SV1.11, X7.C26
VCC: SV1.22, SV1.24, SV1.26, SV1.28, SV1.30, SV1.31, SV1.32, SV1.33, SV1.34, SV1.35, SV1.36, SV1.37, SV1.38, SV1.39, SV1.40, U$5.P$1, U$6.P$1, X1.A1, X1.A2, X1.C1, X1.C2, X2.A1, X2.A2, X2.C1, X2.C2, X3.A1, X3.A2, X3.C1, X3.C2, X4.A1, X4.A2, X4.C1, X4.C2, X5.A1, X5.A2, X5.C1, X5.C2, X6.A1, X6.A2, X6.C1, X6.C2, X7.A1, X7.A2, X7.C1, X7.C2

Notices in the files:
parts and their libraries:
o160650v244+Eagle_WE-RJ45+: Copyright: Würth Elektronik
microchip-smsc-lan8720: (C) 2014 Tomasz Boleslaw CEDRO, cederom@tlen.pl, http://www.tomek.cedro.info.
